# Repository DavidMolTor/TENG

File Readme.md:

# TENG

Research project on TENG energy harvesting.

## Introduction

TODO

## Features

TODO

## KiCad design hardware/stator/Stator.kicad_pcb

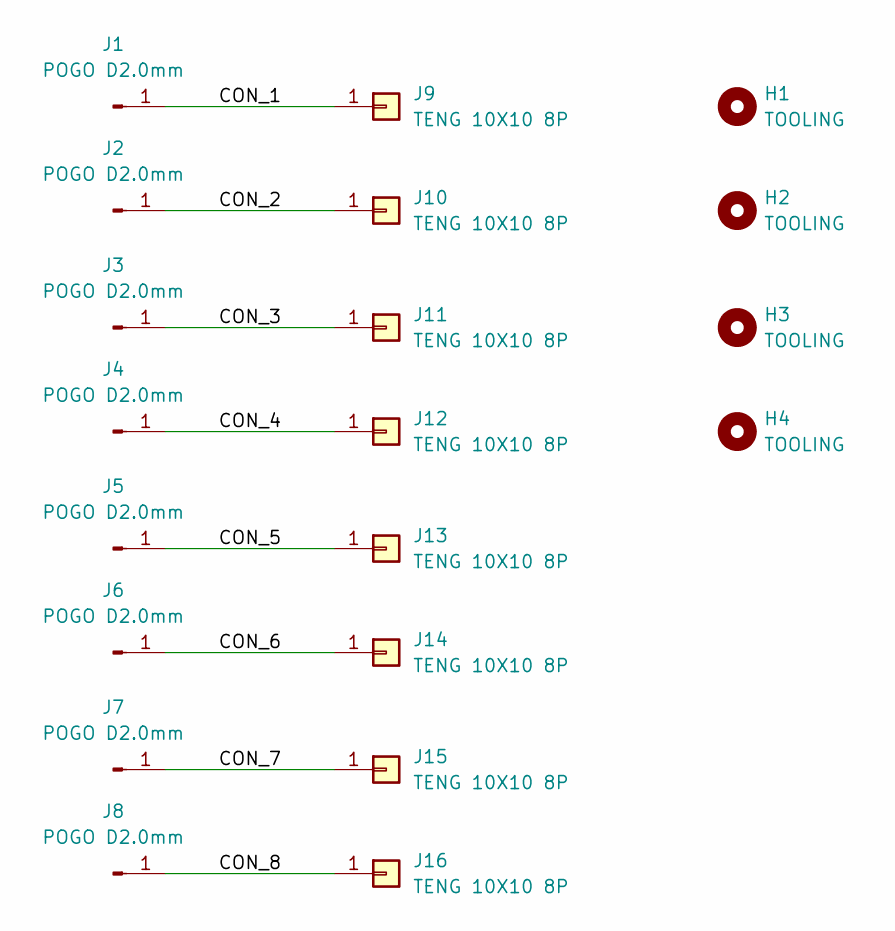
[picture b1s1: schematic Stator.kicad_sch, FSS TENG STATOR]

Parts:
H1, H2, H3, H4: TOOLING; ToolingHole_1.152mm
J1, J2, J3, J4, J5, J6, J7, J8: POGO D2.0mm; PogoPin_D2.0mm_JOIN; Manufacturer Part YZ203115028R-03; JLC Part C5157421
J9, J10, J11, J12, J13, J14, J15, J16: TENG 10X10 8P; CONTACT_CIRCLE_10X10_8P_HUB

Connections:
/CON_1: J1.1 (Pin_1_1), J9.1 (Pin_1_1)
/CON_2: J2.1 (Pin_1_1), J10.1 (Pin_1_1)
/CON_3: J3.1 (Pin_1_1), J11.1 (Pin_1_1)
/CON_4: J4.1 (Pin_1_1), J12.1 (Pin_1_1)
/CON_5: J5.1 (Pin_1_1), J13.1 (Pin_1_1)
/CON_6: J6.1 (Pin_1_1), J14.1 (Pin_1_1)
/CON_7: J7.1 (Pin_1_1), J15.1 (Pin_1_1)
/CON_8: J8.1 (Pin_1_1), J16.1 (Pin_1_1)

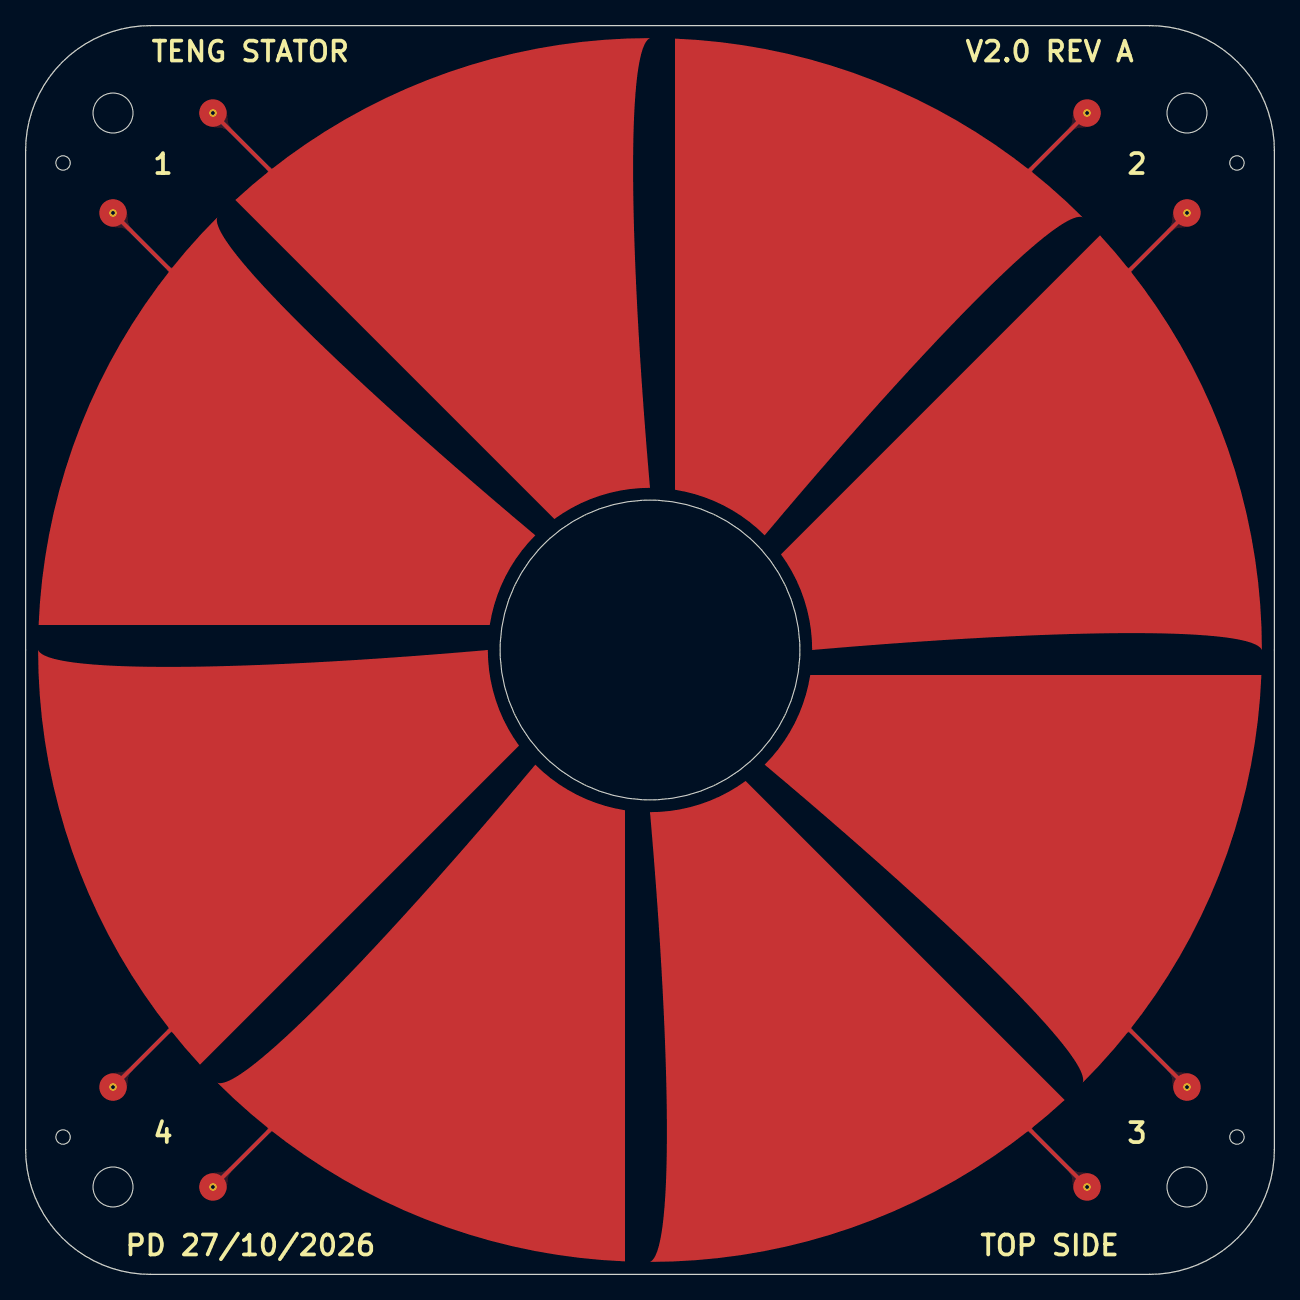
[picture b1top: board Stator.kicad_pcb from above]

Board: 2 copper layers, 100.0 x 100.0 mm, 20 parts (0 on the bottom side), 8 nets.

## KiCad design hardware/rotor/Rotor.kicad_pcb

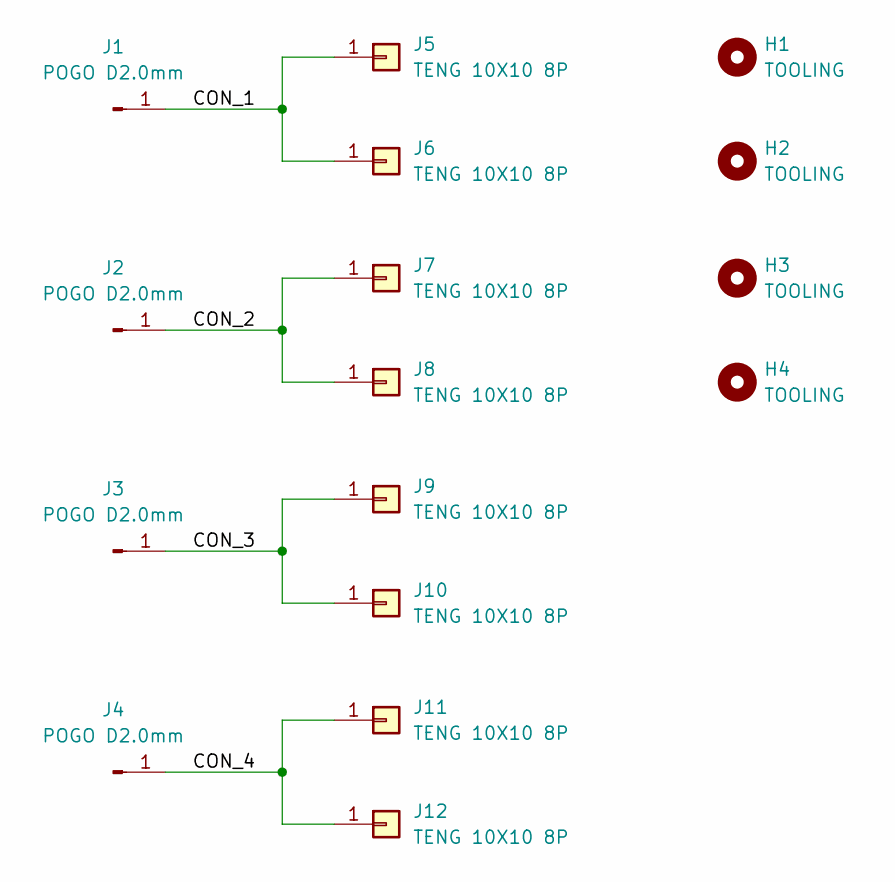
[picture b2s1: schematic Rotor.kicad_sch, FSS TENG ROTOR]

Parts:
H1, H2, H3, H4: TOOLING; ToolingHole_1.152mm
J1, J2, J3, J4: POGO D2.0mm; PogoPin_D2.0mm_JOIN; Manufacturer Part YZ203115028R-03; JLC Part C5157421
J5, J6, J7, J8, J9, J10, J11, J12: TENG 10X10 8P; CONTACT_CIRCLE_10X10_8P

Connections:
/CON_1: J1.1 (Pin_1_1), J5.1 (Pin_1_1), J6.1 (Pin_1_1)
/CON_2: J2.1 (Pin_1_1), J7.1 (Pin_1_1), J8.1 (Pin_1_1)
/CON_3: J3.1 (Pin_1_1), J9.1 (Pin_1_1), J10.1 (Pin_1_1)
/CON_4: J4.1 (Pin_1_1), J11.1 (Pin_1_1), J12.1 (Pin_1_1)

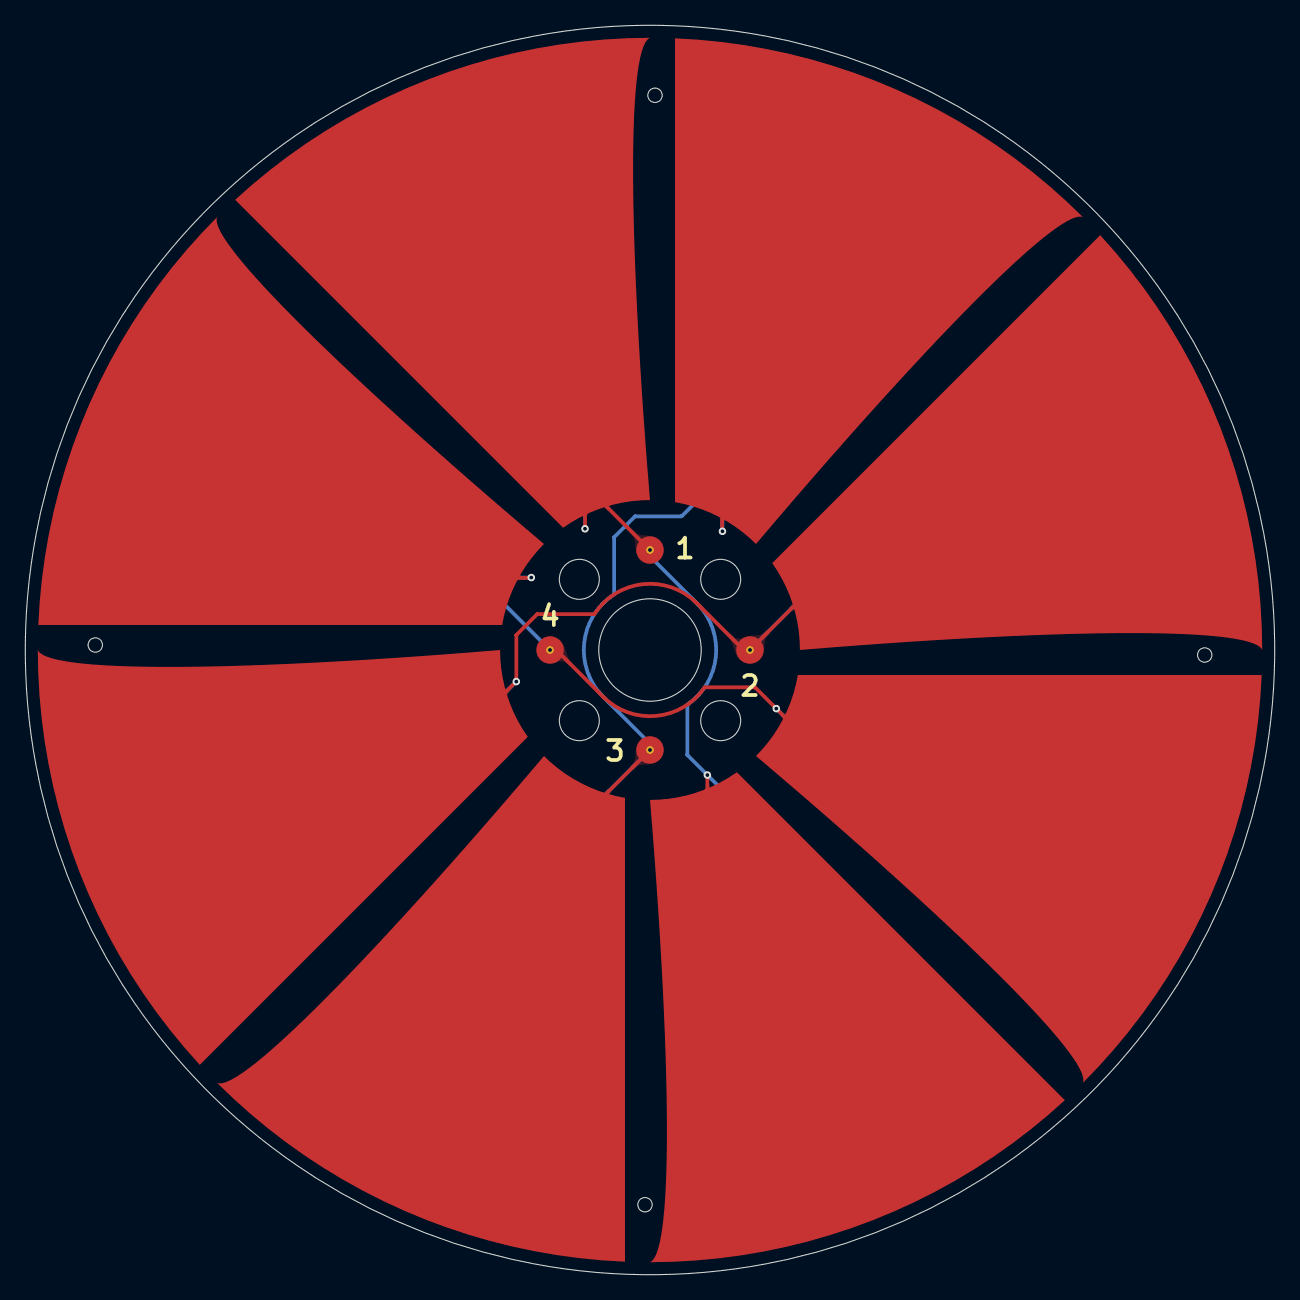
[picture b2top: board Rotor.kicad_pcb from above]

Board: 2 copper layers, 100.0 x 100.0 mm, 16 parts (0 on the bottom side), 4 nets.

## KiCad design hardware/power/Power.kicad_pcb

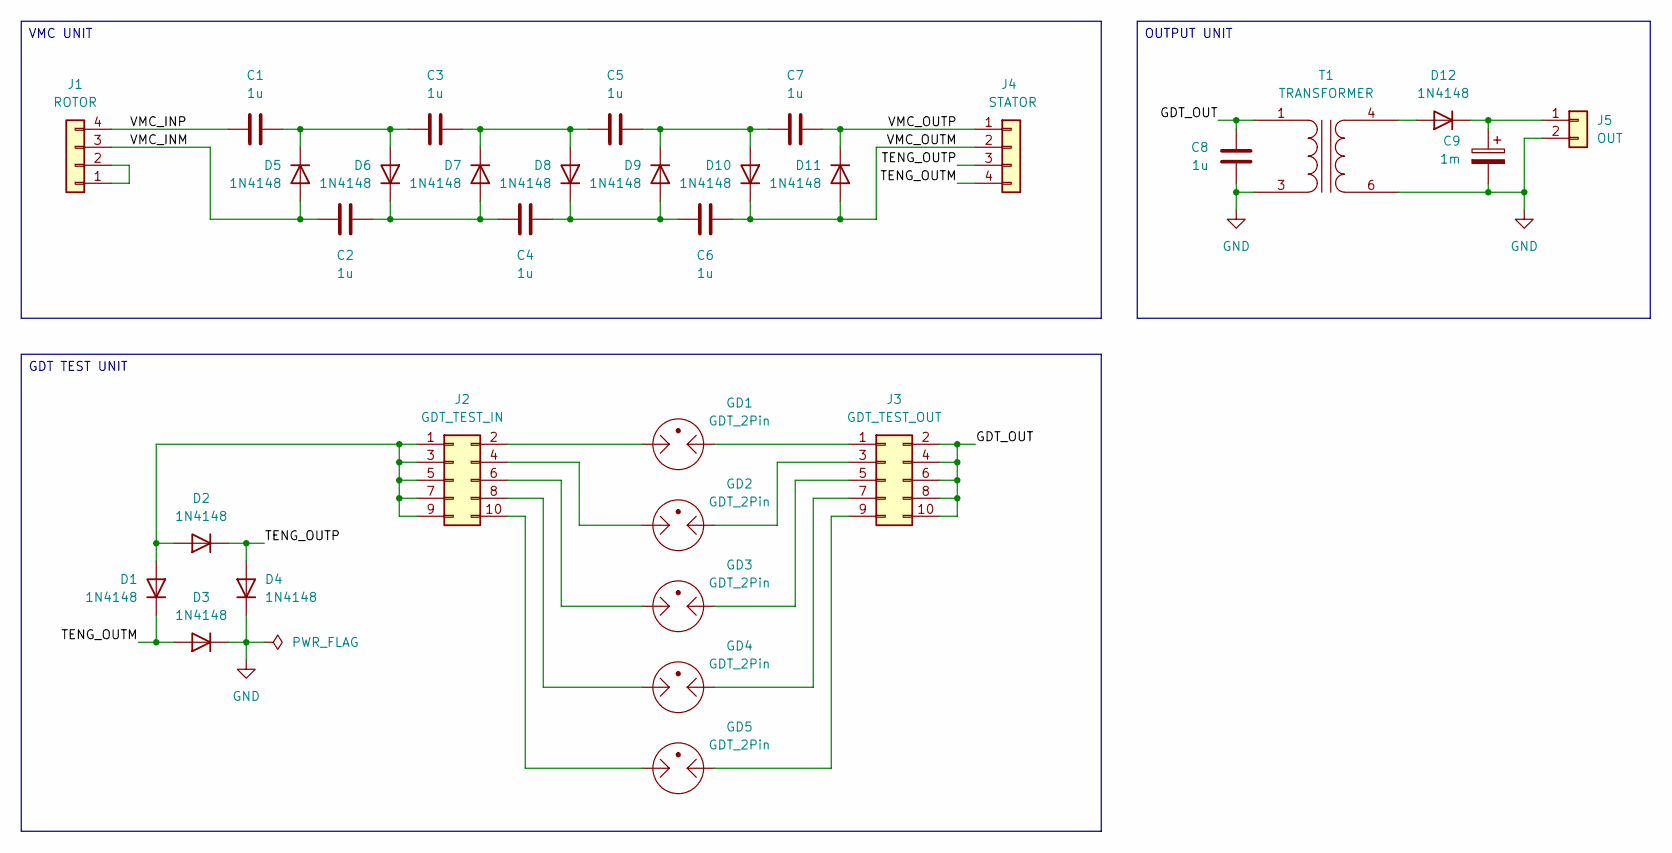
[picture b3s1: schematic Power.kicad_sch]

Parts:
C1, C2, C3, C4, C5, C6, C7, C8: 1u; C_Rect_L10.0mm_W4.0mm_P7.50mm_FKS3_FKP3
C9: 1m; CP_Radial_D17.0mm_P7.50mm
D1, D2, D3, D4, D5, D6, D7, D8, D9, D10, D11, D12: 1N4148; D_DO-35_SOD27_P7.62mm_Horizontal
GD1, GD2, GD3, GD4, GD5: GDT_2Pin; GDT_Bourns_2038
J1: ROTOR; TerminalBlock_Phoenix_MKDS-1,5-4_1x04_P5.00mm_Horizontal
J2: GDT_TEST_IN; PinHeader_2x05_P2.54mm_Vertical
J3: GDT_TEST_OUT; PinHeader_2x05_P2.54mm_Vertical
J4: STATOR; TerminalBlock_Phoenix_MKDS-1,5-4_1x04_P5.00mm_Horizontal
J5: OUT; TerminalBlock_Phoenix_MKDS-1,5-2_1x02_P5.00mm_Horizontal
T1: TRANSFORMER; Transformer_NF_ETAL_P1165

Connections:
/GDT_OUT: C8.1, J3.2, J3.4, J3.6, J3.8, J3.10, T1.1 (AA)
/TENG_OUTM: D1.1 (K), D3.2 (A), J4.4
/TENG_OUTP: D2.1 (K), D4.2 (A), J4.3
/VMC_INM: C2.2, D5.2 (A), J1.3
/VMC_INP: C1.1, J1.4
/VMC_OUTM: C6.1, D10.1 (K), D11.2 (A), J4.2
/VMC_OUTP: C7.2, D11.1 (K), J4.1
GND: C8.2, C9.2, D3.1 (K), D4.1 (K), J5.2, T1.3 (AB), T1.6 (SA)
unnamed: D1.2 (A), D2.2 (A), J2.1, J2.3, J2.5, J2.7, J2.9
unnamed: C1.2, C3.1, D5.1 (K), D6.2 (A)
unnamed: C2.1, C4.2, D6.1 (K), D7.2 (A)
unnamed: C3.2, C5.1, D7.1 (K), D8.2 (A)
unnamed: C4.1, C6.2, D8.1 (K), D9.2 (A)
unnamed: C5.2, C7.1, D9.1 (K), D10.2 (A)
unnamed: D12.2 (A), T1.4 (SB)
unnamed: C9.1, D12.1 (K), J5.1
unnamed: J1.1, J1.2
unnamed: GD1.3, J2.2
unnamed: GD2.3, J2.4
unnamed: GD3.3, J2.6
unnamed: GD4.3, J2.8
unnamed: GD5.3, J2.10
unnamed: GD1.1, J3.1
unnamed: GD2.1, J3.3
unnamed: GD3.1, J3.5
unnamed: GD4.1, J3.7
unnamed: GD5.1, J3.9

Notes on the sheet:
OUTPUT UNIT
GDT TEST UNIT
VMC UNIT

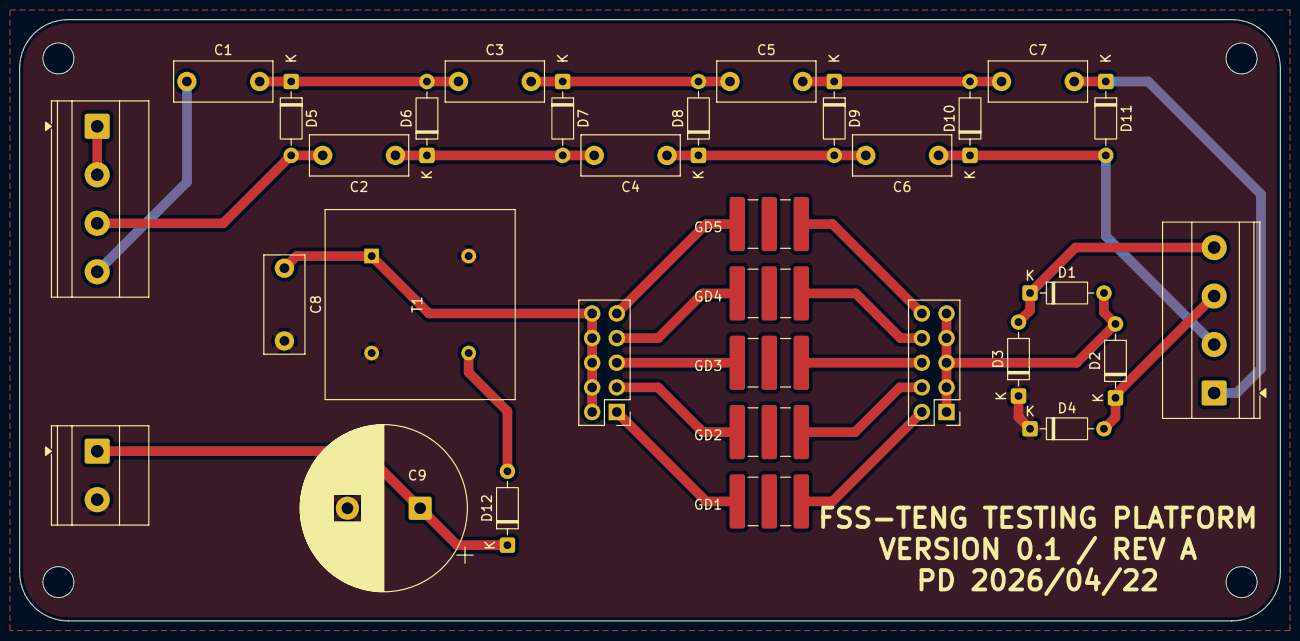
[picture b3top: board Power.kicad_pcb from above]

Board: 2 copper layers, 130.0 x 62.0 mm, 32 parts (0 on the bottom side), 27 nets.

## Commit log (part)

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2026-01-09 Update files
    Updated the ignore file for KiCAD projects.
    Added a license file.
    Added a readme file.
2026-01-10 Generator design files
    Added the rotor PCB design files.
    Added the stator PCB design files.
2026-01-11 Generator design
    Updated the rotor design.
    Updated the stator design.
2026-01-11 Generator models
    Added a rotor 3D model.
    Added a stator 3D model.
2026-01-11 Rotor and generator models
    Updated the rotor design.
    Updated the rotor 3D model.
    Updated the stator 3D model.
2026-01-11 Libraries and generator design
    Updated the generator design.
    Added a libraries folder.
2026-01-12 Generator design
    Updated the rotor board design.
    Updated the stator board design.
2026-01-12 Generator pictures
    Added pictures of the TENG generator boards.
2026-01-25 Simulation and PCB design
    Added an initial FSS TENG simulation profile.
    Added a NEMA17 motor 3D model.
    Updated the stator PCB design.
2026-01-25 Ignore file
    Updated the ignore file definitions.
2026-01-25 Simulation profile
    Updated the TENG simulation profile.
2026-04-22 Project update
    Updated the project to work with KiCad 10.0.
    Updated the exposed pad areas for both layouts.
2026-04-22 Fabrication models
    Added missing models.
    Updated both PCB models.
2026-04-27 TENG layout
    Updated the TENG layout.
    Increased the hub gap area for both layouts.
2026-04-27 Fabrication models
    Updated the fabrication model for the stator.
    Updated the fabrication model for the rotor.
2026-04-27 Testbench models
    Updated the fabrication models for the testbench.
2026-06-24 Simulations
    Updated the simulation files for multiple setups.
    Added simulation models.
2026-06-24 Board layout models
    Updated the rotor PCB layout.
    Updated the stator PCB layout.
    Updated the component models.
2026-06-24 Initial spring article
    Added the initial template for the spring article.
2026-06-24 Power testing
    Added a power testing platform.
2026-06-25 Article body
    Added the main body of the article.
    Missing images and tables.
2026-06-25 First spring article draft
    Updated the main body of the article.
    Added images, tables and references.
2026-06-25 Second spring article draft
    Updated the main body of the article.
    Moved references, images and tables.
